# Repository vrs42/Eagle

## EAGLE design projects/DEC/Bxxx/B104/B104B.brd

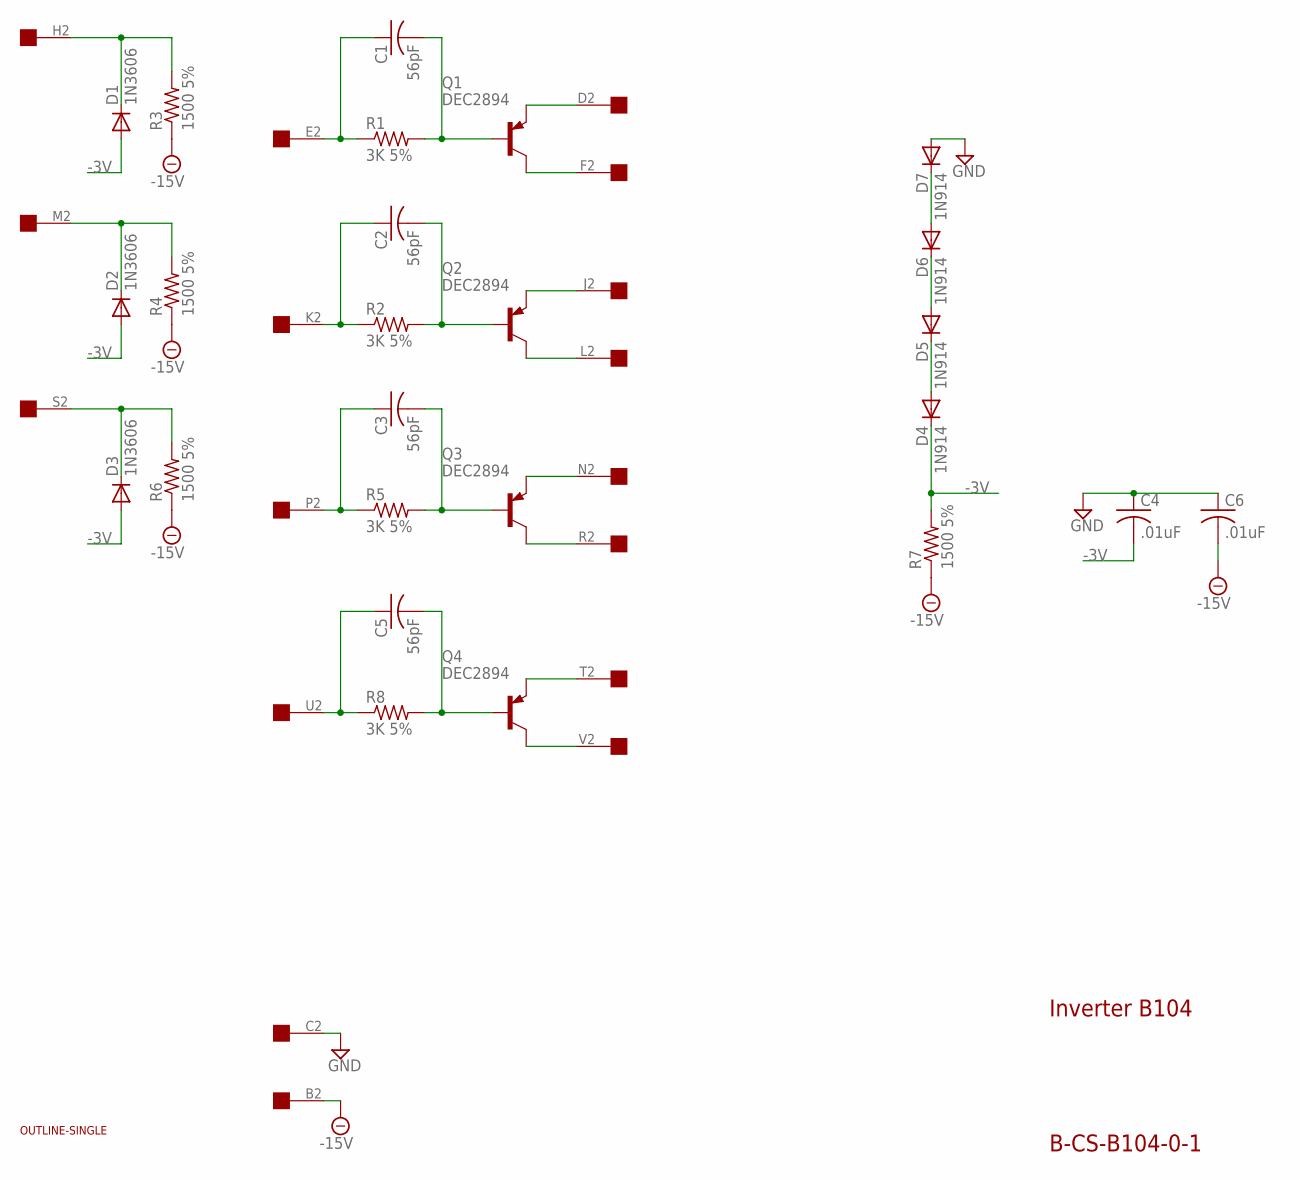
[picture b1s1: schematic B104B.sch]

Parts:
C1, C2, C3, C5: 56pF; C075-032X103
C4, C6: .01uF; C050-025X075
D1, D2, D3: 1N3606; DO35-10
D4, D5, D6, D7: 1N914; DO35-10
Q1, Q2, Q3, Q4: DEC2894; TO39
R1, R2, R5, R8: 3K 5%; 0207/10
R3, R4, R6, R7: 1500 5%; 0207/10
U$1: OUTLINE-SINGLE; SINGLE
U$2: EDGE-1; EDGE-CON1

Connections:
-3V: C4.2, D1.A, D2.A, D3.A, D4.C, R7.2
-15V: C6.2, R3.1, R4.1, R6.1, R7.1, U$2.B2
GND: C4.1, C6.1, D7.A, U$2.C2
unnamed: C1.1, R1.1, U$2.E2
unnamed: Q1.1 (E), U$2.D2
unnamed: C1.2, Q1.2 (B), R1.2
unnamed: Q1.3 (C), U$2.F2
unnamed: D1.C, R3.2, U$2.H2
unnamed: C2.1, R2.1, U$2.K2
unnamed: Q2.1 (E), U$2.J2
unnamed: C2.2, Q2.2 (B), R2.2
unnamed: Q2.3 (C), U$2.L2
unnamed: D2.C, R4.2, U$2.M2
unnamed: C3.1, R5.1, U$2.P2
unnamed: Q3.1 (E), U$2.N2
unnamed: C3.2, Q3.2 (B), R5.2
unnamed: Q3.3 (C), U$2.R2
unnamed: D3.C, R6.2, U$2.S2
unnamed: C5.1, R8.1, U$2.U2
unnamed: Q4.1 (E), U$2.T2
unnamed: C5.2, Q4.2 (B), R8.2
unnamed: Q4.3 (C), U$2.V2
unnamed: D6.A, D7.C
unnamed: D5.A, D6.C
unnamed: D4.A, D5.C

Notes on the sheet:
Inverter B104
B-CS-B104-0-1

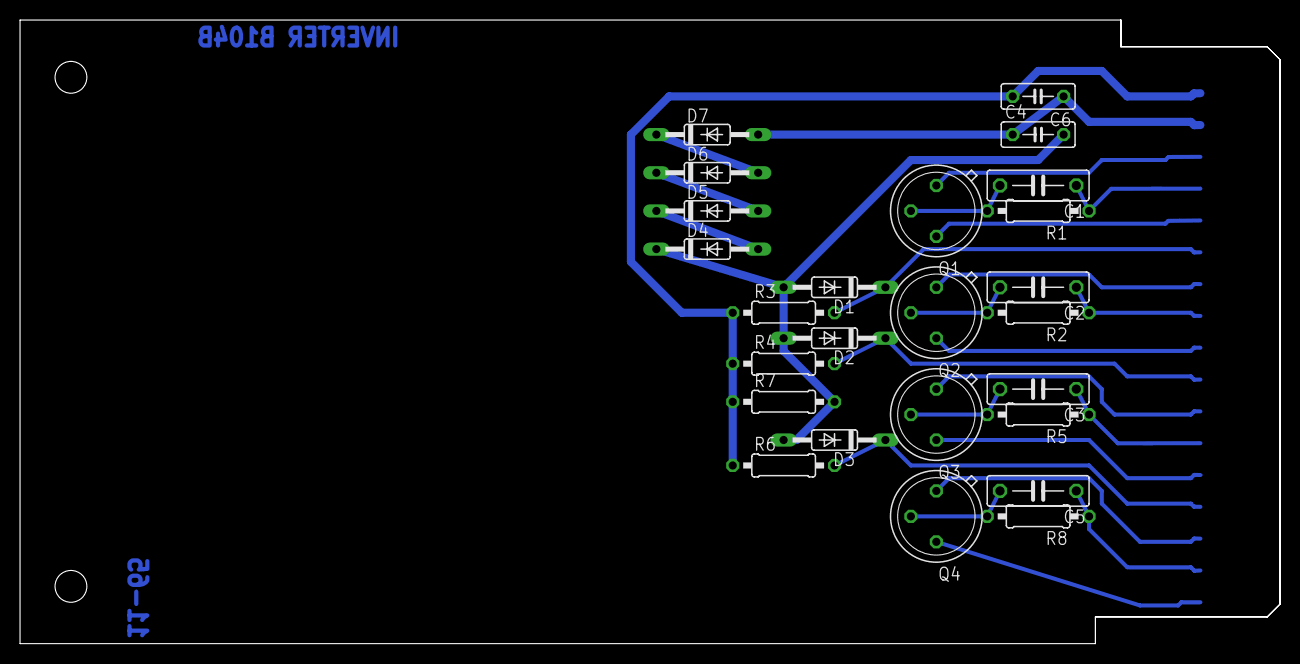
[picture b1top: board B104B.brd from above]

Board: 2 copper layers, 125.7 x 62.2 mm, 27 parts (0 on the bottom side), 25 nets.

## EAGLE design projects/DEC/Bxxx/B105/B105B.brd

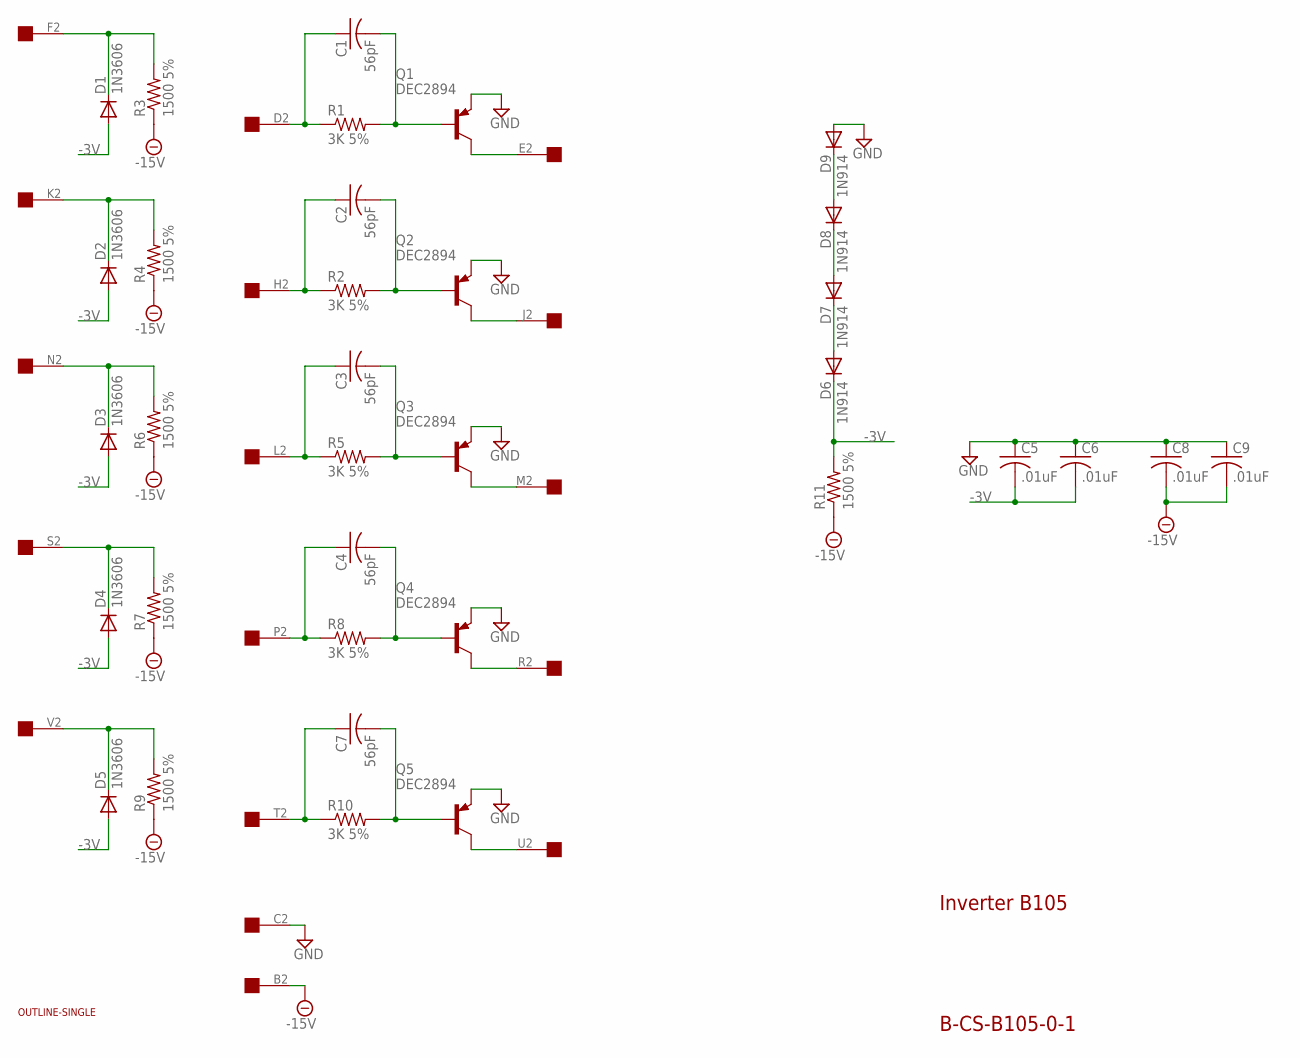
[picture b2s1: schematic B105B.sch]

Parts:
C1, C2, C3, C4, C7: 56pF; C075-032X103
C5, C6, C8, C9: .01uF; C050-025X075
D1, D2, D3, D4, D5: 1N3606; DO35-10
D6, D7, D8, D9: 1N914; DO35-10
Q1, Q2, Q3, Q4, Q5: DEC2894; TO39
R1, R2, R5, R8, R10: 3K 5%; 0207/10
R3, R4, R6, R7, R9, R11: 1500 5%; 0207/10
U$1: OUTLINE-SINGLE; SINGLE
U$2: EDGE-1; EDGE-CON1

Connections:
-3V: C5.2, C6.2, D1.A, D2.A, D3.A, D4.A, D5.A, D6.C, R11.2
-15V: C8.2, C9.2, R3.1, R4.1, R6.1, R7.1, R9.1, R11.1, U$2.B2
GND: C5.1, C6.1, C8.1, C9.1, D9.A, Q1.1 (E), Q2.1 (E), Q3.1 (E), Q4.1 (E), Q5.1 (E), U$2.C2
unnamed: C1.1, R1.1, U$2.D2
unnamed: C1.2, Q1.2 (B), R1.2
unnamed: Q1.3 (C), U$2.E2
unnamed: D1.C, R3.2, U$2.F2
unnamed: C2.1, R2.1, U$2.H2
unnamed: C2.2, Q2.2 (B), R2.2
unnamed: Q2.3 (C), U$2.J2
unnamed: D2.C, R4.2, U$2.K2
unnamed: C3.1, R5.1, U$2.L2
unnamed: C3.2, Q3.2 (B), R5.2
unnamed: Q3.3 (C), U$2.M2
unnamed: D3.C, R6.2, U$2.N2
unnamed: C4.1, R8.1, U$2.P2
unnamed: C4.2, Q4.2 (B), R8.2
unnamed: Q4.3 (C), U$2.R2
unnamed: D4.C, R7.2, U$2.S2
unnamed: C7.1, R10.1, U$2.T2
unnamed: C7.2, Q5.2 (B), R10.2
unnamed: Q5.3 (C), U$2.U2
unnamed: D5.C, R9.2, U$2.V2
unnamed: D8.A, D9.C
unnamed: D7.A, D8.C
unnamed: D6.A, D7.C

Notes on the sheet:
Inverter B105
B-CS-B105-0-1

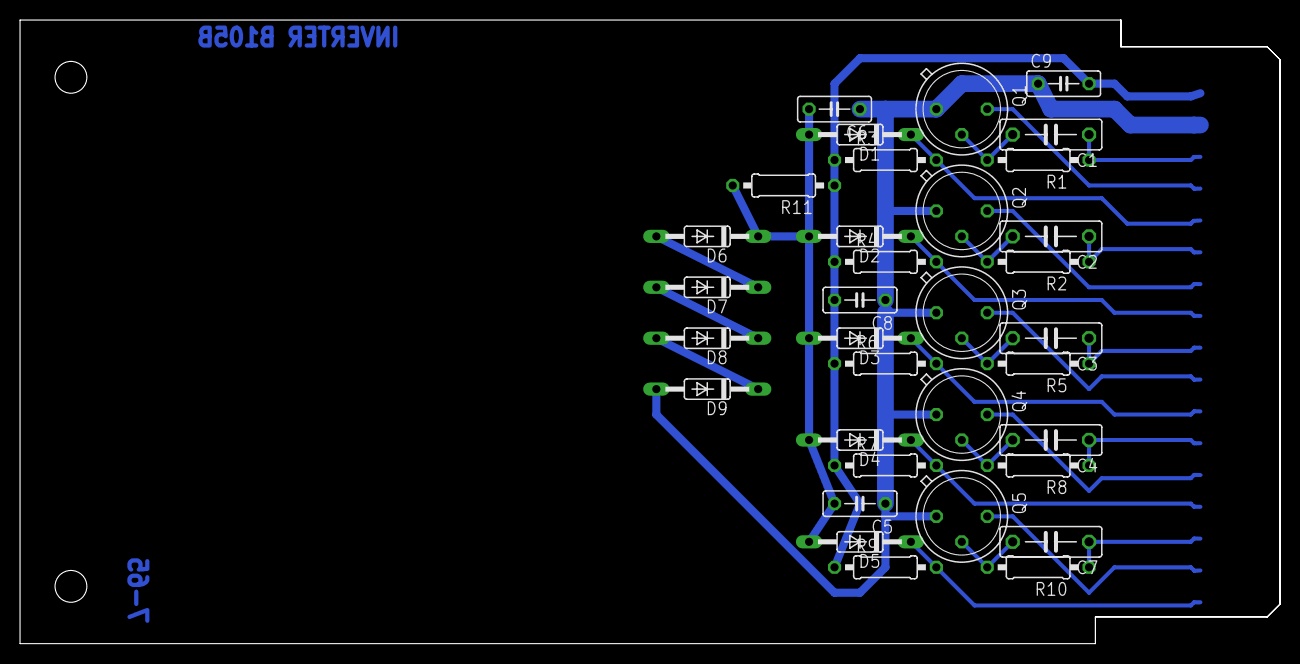
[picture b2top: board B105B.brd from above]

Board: 2 copper layers, 125.7 x 62.2 mm, 36 parts (0 on the bottom side), 26 nets.

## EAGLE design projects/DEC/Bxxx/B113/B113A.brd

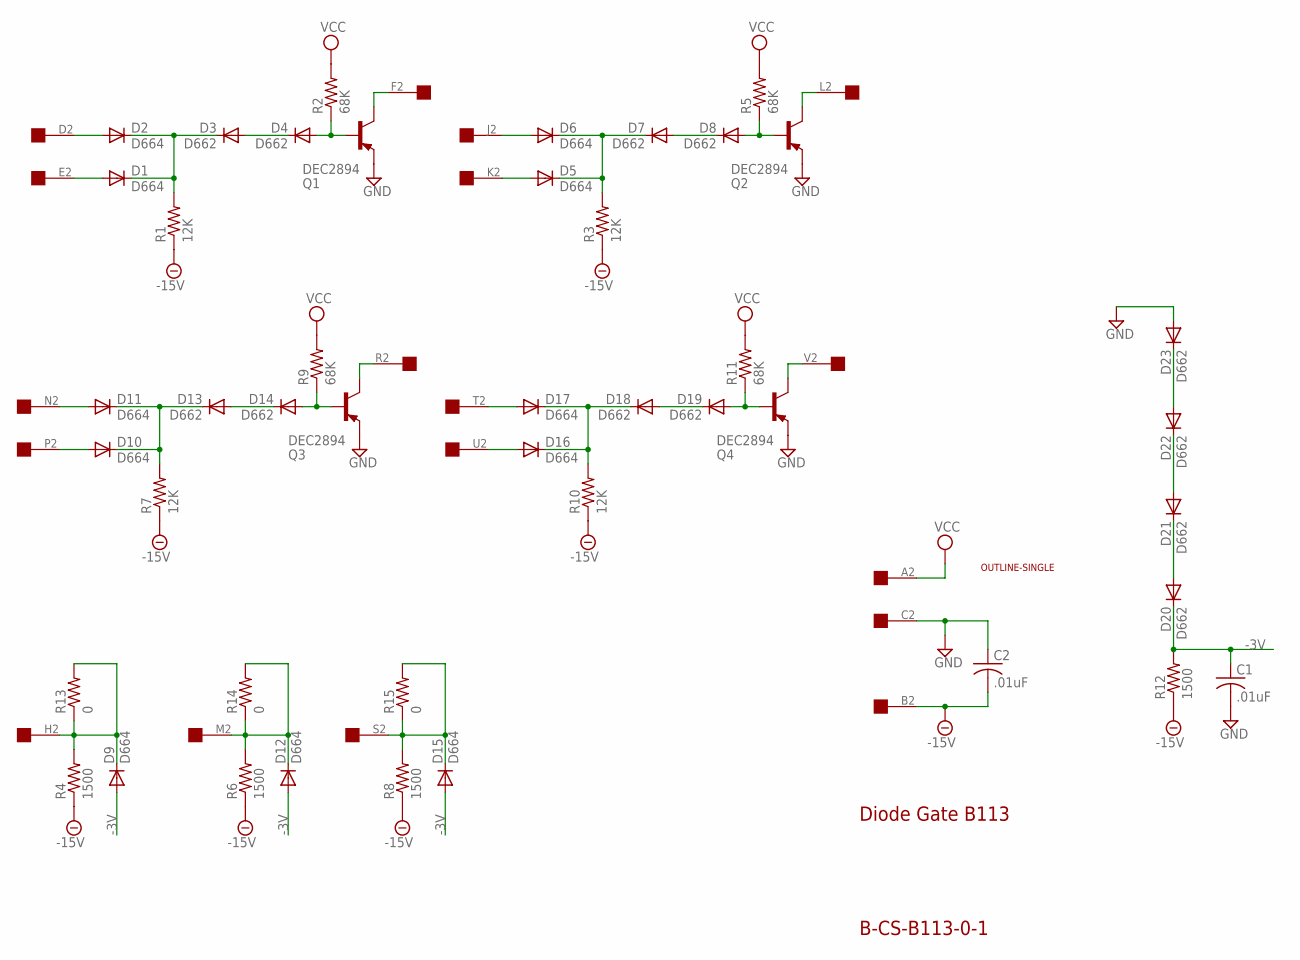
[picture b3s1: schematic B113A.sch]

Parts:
C1, C2: .01uF; C063-025X075
D1, D2, D5, D6, D9, D10, D11, D12, D15, D16, D17: D664; DO35-10
D3, D4, D7, D8, D13, D14, D18, D19, D20, D21, D22, D23: D662; DO35-10
Q1, Q2, Q3, Q4: DEC2894; TO5
R1, R3, R7, R10: 12K; 0207/10
R2, R5, R9, R11: 68K; 0207/10
R4, R6, R8, R12: 1500; 0207/10
R13, R14, R15: 0; 0207/10
U$1: OUTLINE-SINGLE; SINGLE
U$2: EDGE-1; EDGE-CON1

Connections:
-3V: C1.1, D9.A, D12.A, D15.A, D20.C, R12.2
-15V: C2.2, R1.1, R3.1, R4.1, R6.1, R7.1, R8.1, R10.1, R12.1, U$2.B2
GND: C1.2, C2.1, D23.A, Q1.1 (E), Q2.1 (E), Q3.1 (E), Q4.1 (E), U$2.C2
unnamed: D2.A, U$2.D2
unnamed: D1.C, D2.C, D3.C, R1.2
unnamed: D3.A, D4.C
unnamed: D1.A, U$2.E2
unnamed: D4.A, Q1.2 (B), R2.1
unnamed: Q1.3 (C), U$2.F2
unnamed: D9.C, R4.2, R13.1, R13.2, U$2.H2
unnamed: D12.C, R6.2, R14.1, R14.2, U$2.M2
unnamed: D15.C, R8.2, R15.1, R15.2, U$2.S2
unnamed: D6.A, U$2.J2
unnamed: D5.C, D6.C, D7.C, R3.2
unnamed: D7.A, D8.C
unnamed: D5.A, U$2.K2
unnamed: D8.A, Q2.2 (B), R5.1
unnamed: Q2.3 (C), U$2.L2
unnamed: D11.A, U$2.N2
unnamed: D10.C, D11.C, D13.C, R7.2
unnamed: D13.A, D14.C
unnamed: D10.A, U$2.P2
unnamed: D14.A, Q3.2 (B), R9.1
unnamed: Q3.3 (C), U$2.R2
unnamed: D17.A, U$2.T2
unnamed: D16.C, D17.C, D18.C, R10.2
unnamed: D18.A, D19.C
unnamed: D16.A, U$2.U2
unnamed: D19.A, Q4.2 (B), R11.1
unnamed: Q4.3 (C), U$2.V2
unnamed: D22.A, D23.C
unnamed: D21.A, D22.C
unnamed: D20.A, D21.C
VCC: R2.2, R5.2, R9.2, R11.2, U$2.A2

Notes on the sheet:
B-CS-B113-0-1
Diode Gate B113

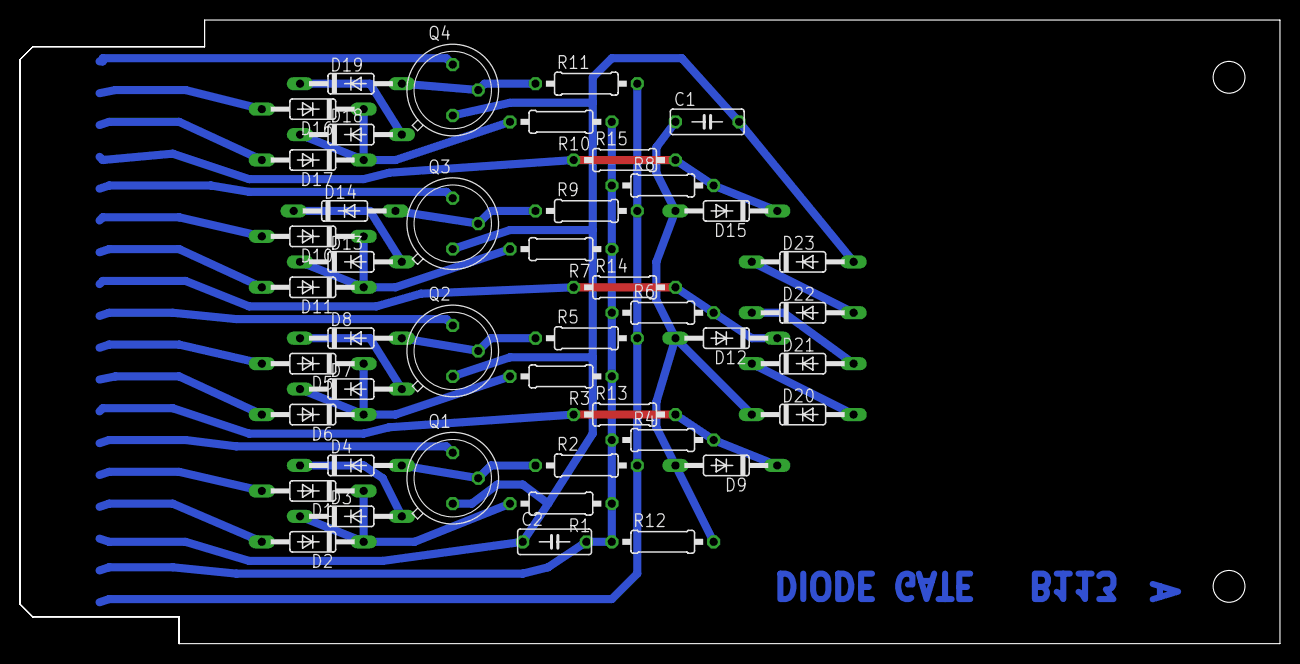
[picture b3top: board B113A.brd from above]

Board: 2 copper layers, 125.7 x 62.2 mm, 46 parts (0 on the bottom side), 34 nets.
